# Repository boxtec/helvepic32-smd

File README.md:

# helvepic32-smd
HelvePic32 SMD

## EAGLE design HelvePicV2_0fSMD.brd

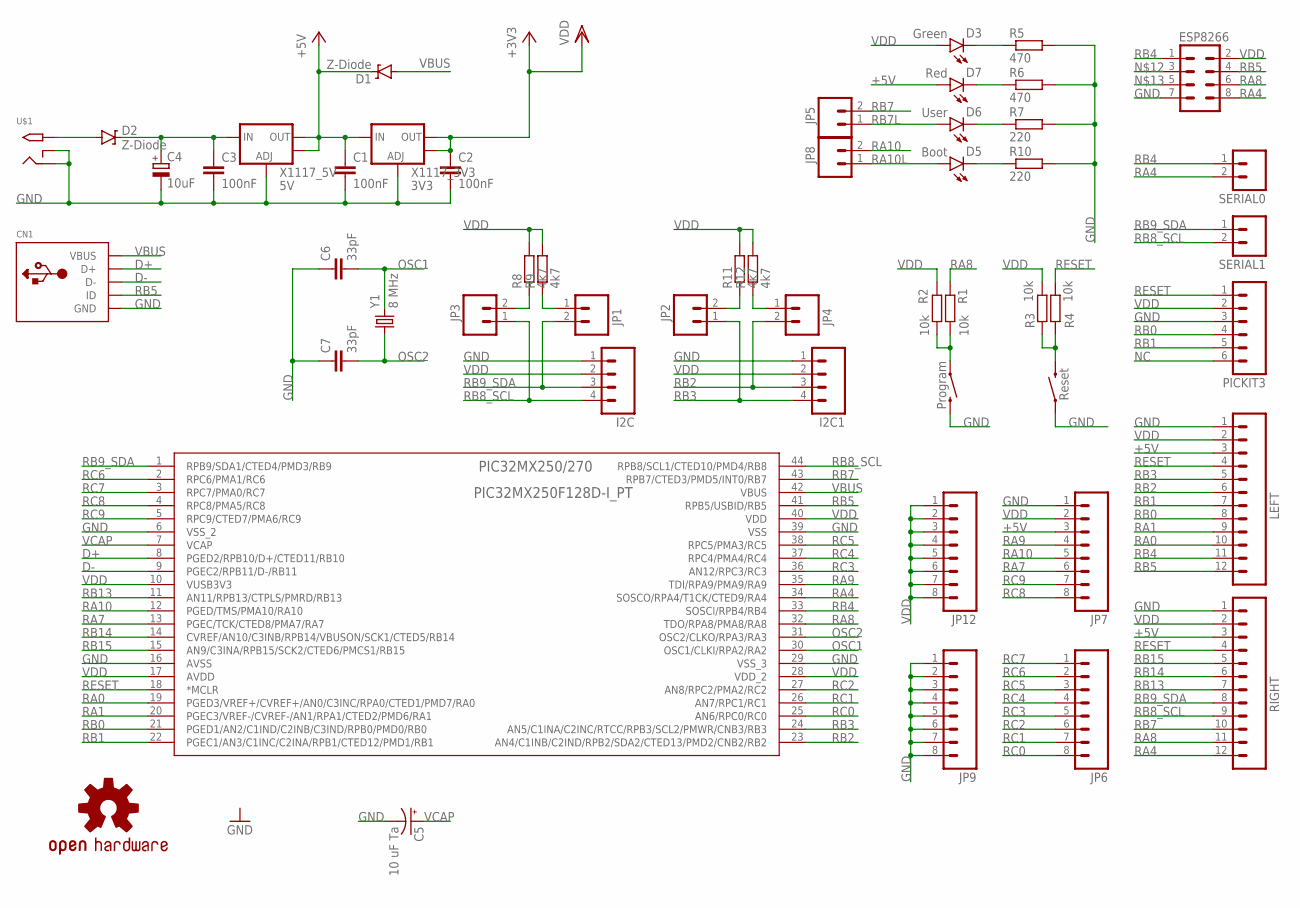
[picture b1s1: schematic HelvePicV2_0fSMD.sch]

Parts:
C1, C2, C3: 100nF; C1206
C4: 10uF; 153CLV-0810
C5: 10 uF Ta; EIA3216
C6, C7: 33pF; C1206
CN1: USBMINIB; USB-MINIB
D1, D2: Z-Diode; SMB-DIODE
D3: Green; LED-1206
D5: Boot; LED-1206
D6: User; LED-1206
D7: Red; LED-1206
ESP8266: M04X2; 2X4
I2C, I2C1: M04PTH; 1X04
JP1, JP2, JP3, JP4, JP5, JP8: M02PTH; 1X02
JP6, JP7, JP9, JP12: M081X08; 1X08
LEFT: M12PTH; 1X12
LOGO1: OSHW-LOGOS; OSHW-LOGO-S
PIC32MX250/270: PIC32MX250F128D-I_PT; QFP44_10X10MC
PICKIT3: M06LOCK; 1X06_LOCK
R1, R2, R3, R4: 10k; R1206
R5, R6: 470; R1206
R7, R10: 220; R1206
R8, R9, R11, R12: 4k7; R1206
RIGHT: M12PTH; 1X12
S1: Program; TACTILE_SWITCH_TALL
S3: Reset; TACTILE_SWITCH_TALL
SERIAL0, SERIAL1: M02PTH; 1X02
U$1: 2.1MMJACKTHM; PJ-102A
X1117_3V3: 3V3; SOT223
X1117_5V: 5V; SOT223
Y1: 8 MHz; HC49UP

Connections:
+5V: C1.1, D1.C, D7.A, JP7.3, LEFT.3, RIGHT.3, X1117_3V3.3 (IN), X1117_5V.2 (OUT), X1117_5V.4 (OUT)
D+: CN1.D+, PIC32MX250/270.8 (PGED2/RPB10/D+/CTED11/RB10)
D-: CN1.D-, PIC32MX250/270.9 (PGEC2/RPB11/D-/RB11)
GND: C1.2, C2.2, C3.2, C4.-, C5.C (-), C6.1, C7.1, CN1.GND, ESP8266.7, I2C.1, I2C1.1, JP7.1, JP9.1, JP9.2, JP9.3, JP9.4, JP9.5, JP9.6, JP9.7, JP9.8, LEFT.1, PIC32MX250/270.6 (VSS_2), PIC32MX250/270.16 (AVSS), PIC32MX250/270.29 (VSS_3), PIC32MX250/270.39 (VSS), PICKIT3.3, R5.2, R6.2, R7.2, R10.2, RIGHT.1, S1.B2 (2), S3.A2 (1), U$1.RING, U$1.RING_SW, X1117_3V3.1 (ADJ), X1117_5V.1 (ADJ)
unnamed: JP3.2, R8.1
unnamed: D3.C, R5.1
unnamed: D7.C, R6.1
unnamed: JP1.1, R9.1
unnamed: D2.A, U$1.TIP
unnamed: JP2.2, R11.1
unnamed: JP4.1, R12.1
unnamed: C3.1, C4.+, D2.C, X1117_5V.3 (IN)
unnamed: R1.2, R2.2, S1.A2 (1)
unnamed: R3.1, R4.1, S3.B2 (2)
NC: PICKIT3.6
OSC1: C6.2, PIC32MX250/270.30 (OSC1/CLKI/RPA2/RA2), Y1.2
OSC2: C7.2, PIC32MX250/270.31 (OSC2/CLKO/RPA3/RA3), Y1.1
RA0: LEFT.10, PIC32MX250/270.19 (PGED3/VREF+/CVREF+/AN0/C3INC/RPA0/CTED1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)
RA1: LEFT.9, PIC32MX250/270.20 (PGEC3/VREF-/CVREF-/AN1/RPA1/CTED2/PMD6/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)
RA4: ESP8266.8, PIC32MX250/270.34 (SOSCO/RPA4/T1CK/CTED9/RA4), RIGHT.12, SERIAL0.2
RA7: JP7.6, PIC32MX250/270.13 (PGEC/TCK/CTED8/PMA7/RA7)
RA8: ESP8266.6, PIC32MX250/270.32 (TDO/RPA8/PMA8/RA8), R1.1, RIGHT.11
RA9: JP7.4, PIC32MX250/270.35 (TDI/RPA9/PMA9/RA9)
RA10: JP7.5, JP8.2, PIC32MX250/270.12 (PGED/TMS/PMA10/RA10)
RA10L: D5.A, JP8.1
RB0: LEFT.8, PIC32MX250/270.21 (PGED1/AN2/C1IND/C2INB/C3IND/RPB0/PMD0/R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), PICKIT3.4
RB1: LEFT.7, PIC32MX250/270.22 (PGEC1/AN3/C1INC/C2INA/RPB1/CTED12/PMD1/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), PICKIT3.5
RB2: I2C1.3, JP4.2, LEFT.6, PIC32MX250/270.23 (AN4/C1INB/C2IND/RPB2/SDA2/CTED13/PMD2/C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)
RB3: I2C1.4, JP2.1, LEFT.5, PIC32MX250/270.24 (AN5/C1INA/C2INC/RTCC/RPB3/SCL2/PMWR/CNB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)
RB4: ESP8266.1, LEFT.11, PIC32MX250/270.33 (SOSCI/RPB4/RB4), SERIAL0.1
RB5: CN1.ID, ESP8266.4, LEFT.12, PIC32MX250/270.41 (RPB5/USBID/RB5)
RB7: JP5.2, PIC32MX250/270.43 (RPB7/CTED3/PMD5/INT0/RB7), RIGHT.10
RB7L: D6.A, JP5.1
RB8_SCL: I2C.4, JP3.1, PIC32MX250/270.44 (RPB8/SCL1/CTED10/PMD4/RB8), RIGHT.9, SERIAL1.2
RB9_SDA: I2C.3, JP1.2, PIC32MX250/270.1 (RPB9/SDA1/CTED4/PMD3/RB9), RIGHT.8, SERIAL1.1
RB13: PIC32MX250/270.11 (AN11/RPB13/CTPLS/PMRD/RB13), RIGHT.7
RB14: PIC32MX250/270.14 (CVREF/AN10/C3INB/RPB14/VBUSON/SCK1/CTED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), RIGHT.6
RB15: PIC32MX250/270.15 (AN9/C3INA/RPB15/SCK2/CTED6/PMCS1/RB15), RIGHT.5
RC0: JP6.8, PIC32MX250/270.25 (AN6/RPC0/RC0)
RC1: JP6.7, PIC32MX250/270.26 (AN7/RPC1/RC1)
RC2: JP6.6, PIC32MX250/270.27 (AN8/RPC2/PMA2/RC2)
RC3: JP6.5, PIC32MX250/270.36 (AN12/RPC3/RC3)
RC4: JP6.4, PIC32MX250/270.37 (RPC4/PMA4/RC4)
RC5: JP6.3, PIC32MX250/270.38 (RPC5/PMA3/RC5)
RC6: JP6.2, PIC32MX250/270.2 (RPC6/PMA1/RC6)
RC7: JP6.1, PIC32MX250/270.3 (RPC7/PMA0/RC7)
RC8: JP7.8, PIC32MX250/270.4 (RPC8/PMA5/RC8)
RC9: JP7.7, PIC32MX250/270.5 (RPC9/CTED7/PMA6/RC9)
RESET: LEFT.4, PIC32MX250/270.18 (*MCLR), PICKIT3.1, R4.2, RIGHT.4
VBUS: CN1.VBUS, D1.A, PIC32MX250/270.42 (VBUS)
VCAP: C5.A (+), PIC32MX250/270.7 (VCAP)
VDD: C2.1, D3.A, ESP8266.2, I2C.2, I2C1.2, JP7.2, JP12.1, JP12.2, JP12.3, JP12.4, JP12.5, JP12.6, JP12.7, JP12.8, LEFT.2, PIC32MX250/270.10 (VUSB3V3), PIC32MX250/270.17 (AVDD), PIC32MX250/270.28 (VDD_2), PIC32MX250/270.40 (VDD), PICKIT3.2, R2.1, R3.2, R8.2, R9.2, R11.2, R12.2, RIGHT.2, X1117_3V3.2 (OUT), X1117_3V3.4 (OUT)
YELLOW: D6.C, R7.1
YELLOW1: D5.C, R10.1

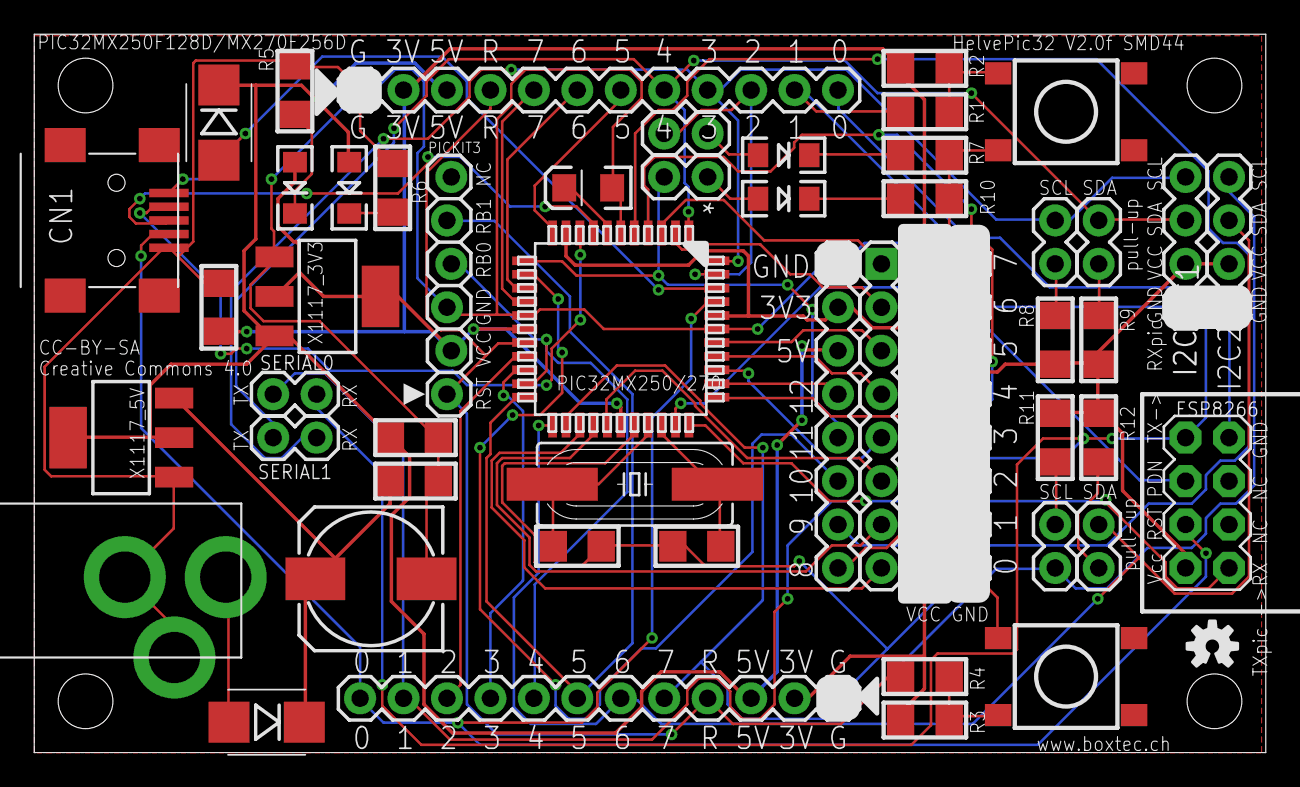
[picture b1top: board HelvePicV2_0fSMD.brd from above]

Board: 2 copper layers, 72.0 x 42.0 mm, 52 parts (0 on the bottom side), 53 nets.

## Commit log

2017-02-28 Initial git import

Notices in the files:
HelvePicV2_0fSMD.brd:
CC-BY-SA
Creative Commons 4.0
parts and their libraries:
SparkFun-Capacitors: Licensing: Creative Commons ShareAlike 4.0 International - https://creativecommons.org/licenses/by-sa/4.0
